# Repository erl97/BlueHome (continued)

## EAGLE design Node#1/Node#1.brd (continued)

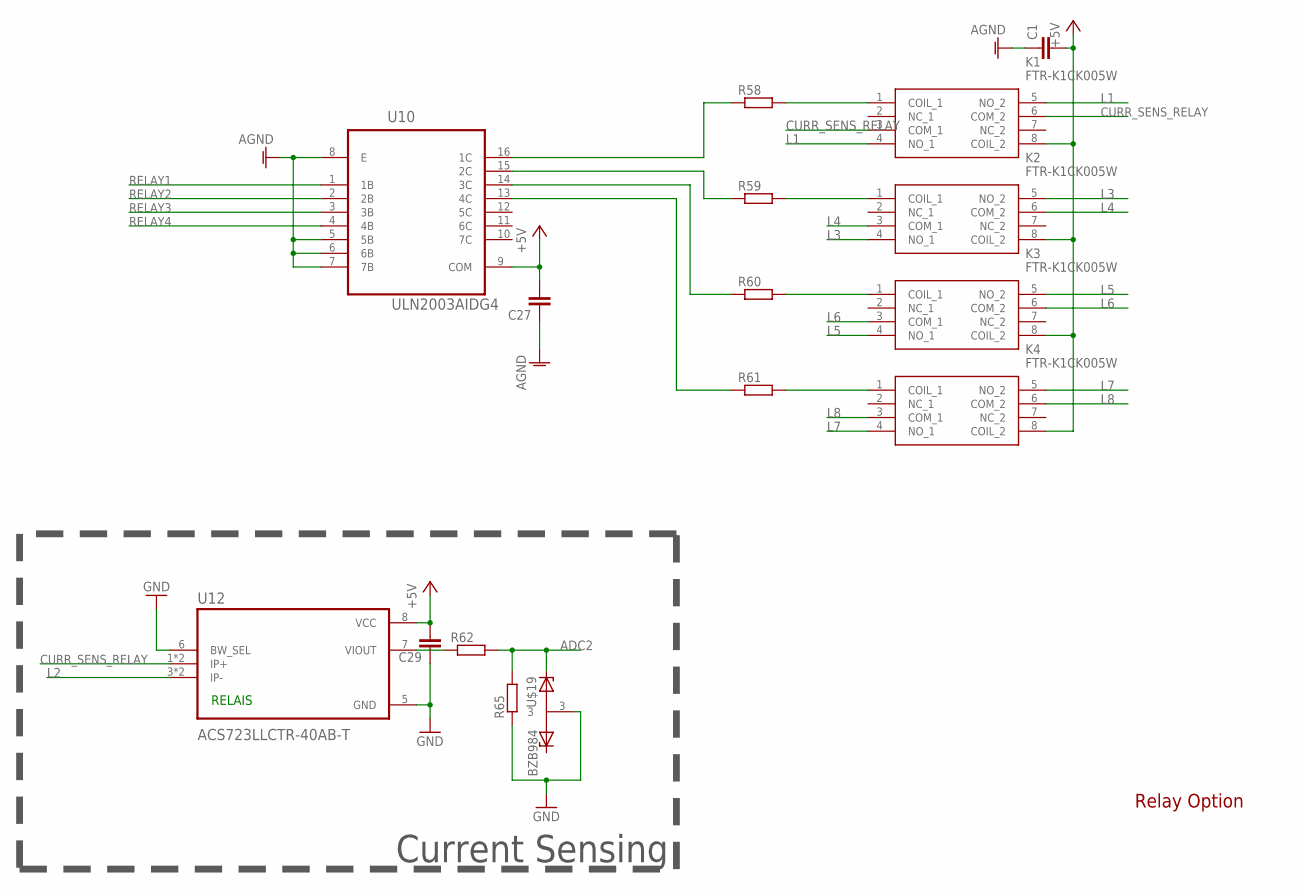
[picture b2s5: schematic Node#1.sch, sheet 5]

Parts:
C1, C27, C29: C-EUC0805; C0805
K1, K2, K3, K4: FTR-K1CK005W; FTRK1CK005W
R58, R59, R60, R61: R-EU_M0805; M0805
R62, R65: R-EU_R0805; R0805
U10: ULN2003AIDG4; SOIC127P600X175-16N
U12: ACS723LLCTR-40AB-T; SOIC127P600X175-8N
U$19: BZB984; SOT95P230X110-3N

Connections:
+5V: C1.2, C27.2, C29.2, K1.8 (COIL_2), K2.8 (COIL_2), K3.8 (COIL_2), K4.8 (COIL_2), U10.9 (COM), U12.8 (VCC); also elsewhere on the board
ADC2: R62.2, R65.2, U$19.1; also elsewhere on the board
AGND: C1.1, C27.1, U10.5 (5B), U10.6 (6B), U10.7 (7B), U10.8 (E); also elsewhere on the board
CURR_SENS_RELAY: K1.3 (COM_1), K1.6 (COM_2), U12.1 (IP+), U12.2 (IP+)
GND: C29.1, R65.1, U12.5 (GND), U12.6 (BW_SEL), U$19.3; also elsewhere on the board
L1: K1.4 (NO_1), K1.5 (NO_2); also elsewhere on the board
L2: U12.3 (IP-), U12.4 (IP-); also elsewhere on the board
L3: K2.4 (NO_1), K2.5 (NO_2); also elsewhere on the board
L4: K2.3 (COM_1), K2.6 (COM_2); also elsewhere on the board
L5: K3.4 (NO_1), K3.5 (NO_2); also elsewhere on the board
L6: K3.3 (COM_1), K3.6 (COM_2); also elsewhere on the board
L7: K4.4 (NO_1), K4.5 (NO_2); also elsewhere on the board
L8: K4.3 (COM_1), K4.6 (COM_2); also elsewhere on the board
unnamed: K1.1 (COIL_1), R58.2
unnamed: K2.1 (COIL_1), R59.2
unnamed: K3.1 (COIL_1), R60.2
unnamed: K4.1 (COIL_1), R61.2
unnamed: R58.1, U10.16 (1C)
unnamed: R59.1, U10.15 (2C)
unnamed: R60.1, U10.14 (3C)
unnamed: R61.1, U10.13 (4C)
unnamed: R62.1, U12.7 (VIOUT)
RELAY1: U10.1 (1B); also elsewhere on the board
RELAY2: U10.2 (2B); also elsewhere on the board
RELAY3: U10.3 (3B); also elsewhere on the board
RELAY4: U10.4 (4B); also elsewhere on the board

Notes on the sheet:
RELAIS
Current Sensing
Relay Option

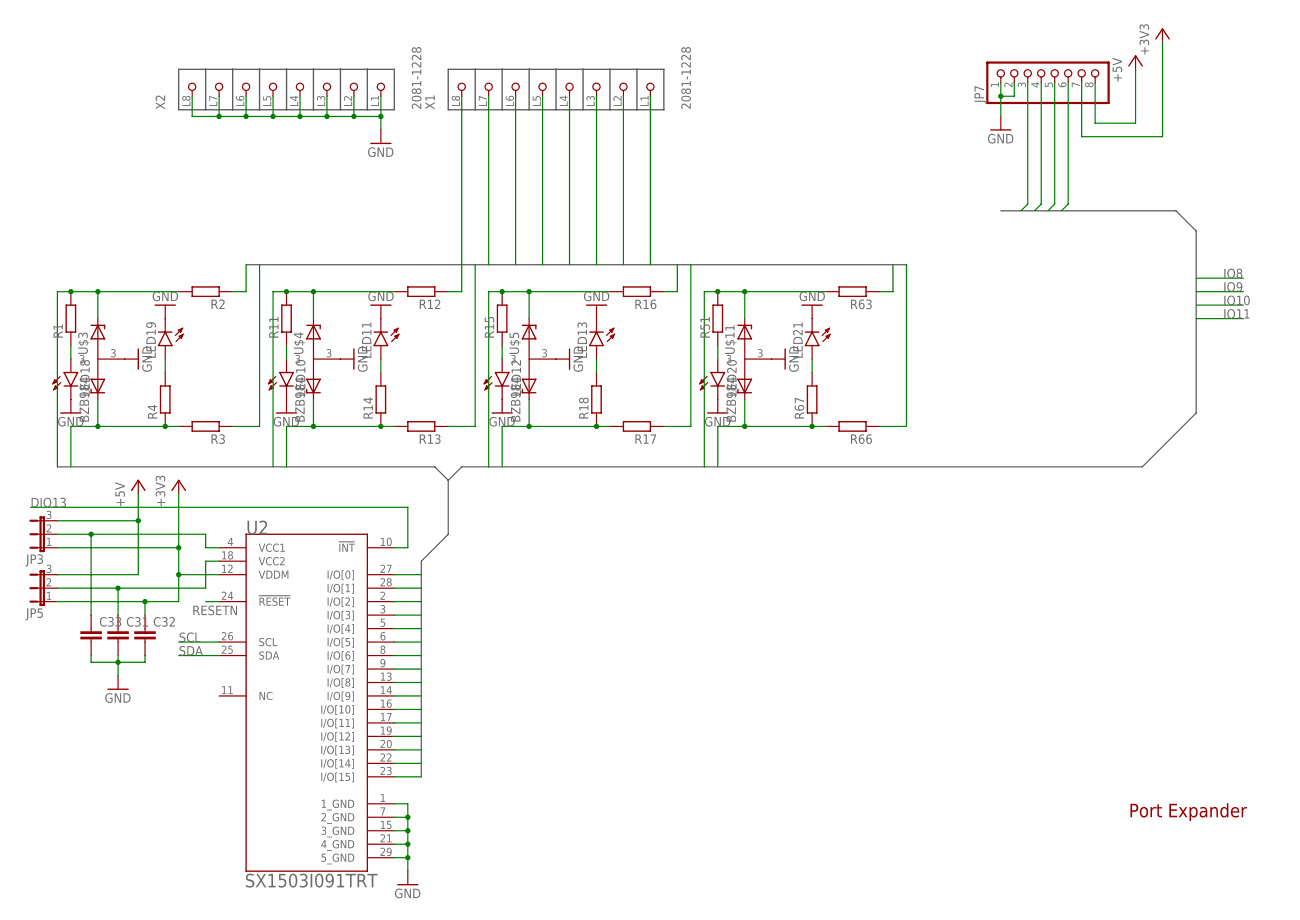
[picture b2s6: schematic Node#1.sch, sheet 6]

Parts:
C31, C32, C33: C-EUC0805; C0805
JP3, JP5: JP2E; JP2
JP7: PINHD-1X8; 1X08
LED10, LED11, LED12, LED13, LED18, LED19, LED20, LED21: LED3MM
R1, R2, R3, R4, R11, R12, R13, R14, R15, R16, R17, R18, R51, R63, R66, R67: R-EU_R0805; R0805
U2: SEMTECH_SX1503I091TRTSEMTECH_SX1503I091TRT_0_0; SEMTECH_SX1503I091TRT_0
U$3, U$4, U$5, U$11: BZB984; SOT95P230X110-3N
X1, X2: 2081-1228; P-2081-1228

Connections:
+3V3: C32.1, JP3.1, JP5.1, JP7.7, U2.12 (VDDM); also elsewhere on the board
+5V: JP3.3, JP5.3, JP7.8; also elsewhere on the board
DIO13: U2.10 (!INT!); also elsewhere on the board
GND: C31.2, C32.2, C33.2, JP7.1, JP7.2, LED10.K (C), LED11.K (C), LED12.K (C), LED13.K (C), LED18.K (C), LED19.K (C), LED20.K (C), LED21.K (C), U2.1 (1_GND), U2.7 (2_GND), U2.15 (3_GND), U2.21 (4_GND), U2.29 (5_GND), U$3.3, U$4.3, U$5.3, U$11.3, X2.L1 (P1), X2.L2 (P2), X2.L3 (P3), X2.L4 (P4), X2.L5 (P5), X2.L6 (P6), X2.L7 (P7), X2.L8 (P8); also elsewhere on the board
IO0: R1.2, R2.2, U2.27 (I/O[0]), U$3.1
IO1: R3.2, R4.1, U2.28 (I/O[1]), U$3.2
IO2: R11.2, R12.2, U2.2 (I/O[2]), U$4.1
IO3: R13.2, R14.1, U2.3 (I/O[3]), U$4.2
IO4: R15.2, R16.2, U2.5 (I/O[4]), U$5.1
IO5: R17.2, R18.1, U2.6 (I/O[5]), U$5.2
IO6: R51.2, R63.2, U2.8 (I/O[6]), U$11.1
IO7: R66.2, R67.1, U2.9 (I/O[7]), U$11.2
IO8: U2.13 (I/O[8]); also elsewhere on the board
IO9: U2.14 (I/O[9]); also elsewhere on the board
IO10: U2.16 (I/O[10]); also elsewhere on the board
IO11: U2.17 (I/O[11]); also elsewhere on the board
IO12: JP7.3, U2.19 (I/O[12])
IO13: JP7.4, U2.20 (I/O[13])
IO14: JP7.5, U2.22 (I/O[14])
IO15: JP7.6, U2.23 (I/O[15])
unnamed: LED18.A, R1.1
unnamed: LED19.A, R4.2
unnamed: LED10.A, R11.1
unnamed: LED11.A, R14.2
unnamed: LED12.A, R15.1
unnamed: LED13.A, R18.2
unnamed: LED20.A, R51.1
unnamed: LED21.A, R67.2
unnamed: C33.1, JP3.2, U2.4 (VCC1)
unnamed: C31.1, JP5.2, U2.18 (VCC2)
O_IO0: R2.1, X1.L1 (P1)
O_IO1: R3.1, X1.L2 (P2)
O_IO2: R12.1, X1.L3 (P3)
O_IO3: R13.1, X1.L4 (P4)
O_IO4: R16.1, X1.L5 (P5)
O_IO5: R17.1, X1.L6 (P6)
O_IO6: R63.1, X1.L7 (P7)
O_IO7: R66.1, X1.L8 (P8)
RESETN: U2.24 (!RESET!); also elsewhere on the board
SCL: U2.26 (SCL); also elsewhere on the board
SDA: U2.25 (SDA); also elsewhere on the board

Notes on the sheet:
Port Expander

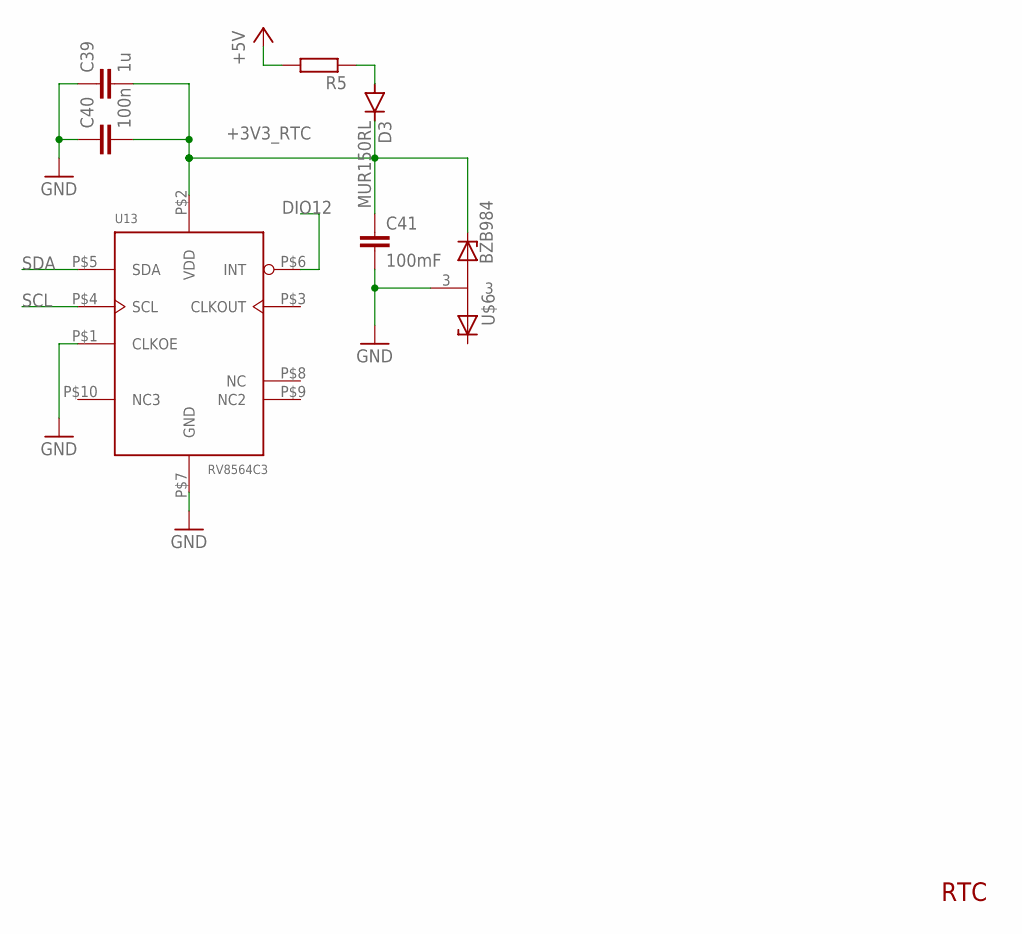
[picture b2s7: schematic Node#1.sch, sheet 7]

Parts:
C39: 1u; C0805
C40: 100n; C0805
C41: 100mF; C050-055X075
D3: MUR150RL; DO41-10
R5: R-EU_R0805; R0805
U13: RV8564C3; RTC-C3
U$6: BZB984; SOT95P230X110-3N

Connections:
+3V3_RTC: C39.2, C40.2, C41.1, D3.C, U13.P$2 (VDD), U$6.2
+5V: R5.2; also elsewhere on the board
DIO12: U13.P$6 (INT); also elsewhere on the board
GND: C39.1, C40.1, C41.2, U13.P$1 (CLKOE), U13.P$7 (GND), U$6.3; also elsewhere on the board
unnamed: D3.A, R5.1
SCL: U13.P$4 (SCL); also elsewhere on the board
SDA: U13.P$5 (SDA); also elsewhere on the board

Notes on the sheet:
RTC

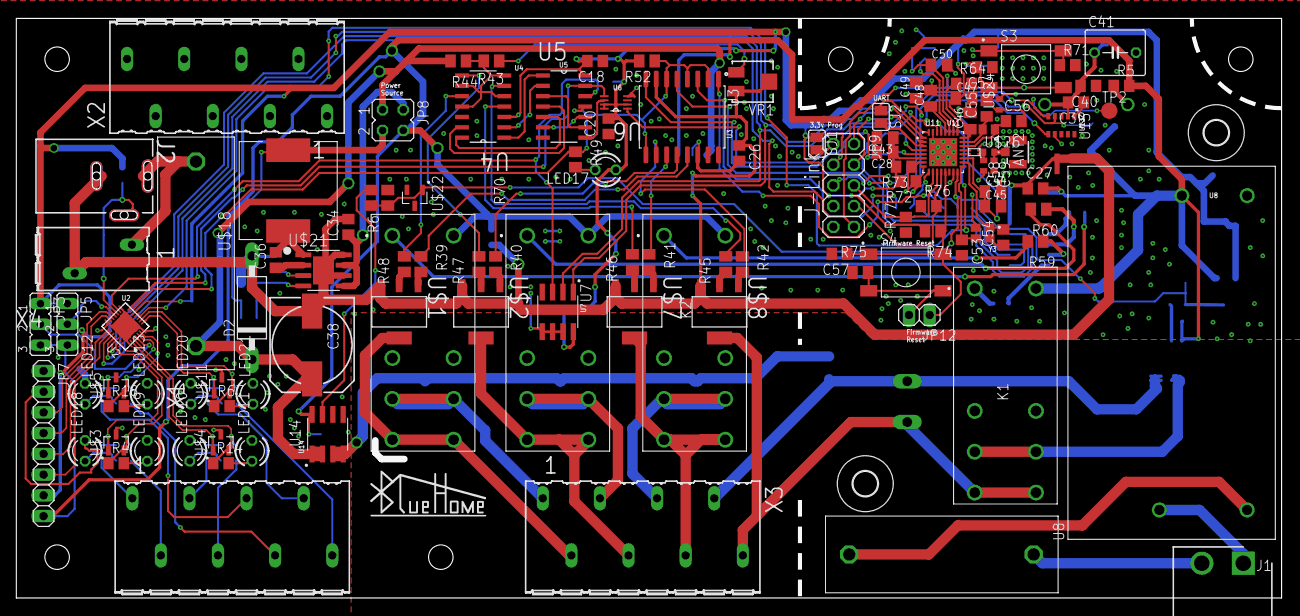
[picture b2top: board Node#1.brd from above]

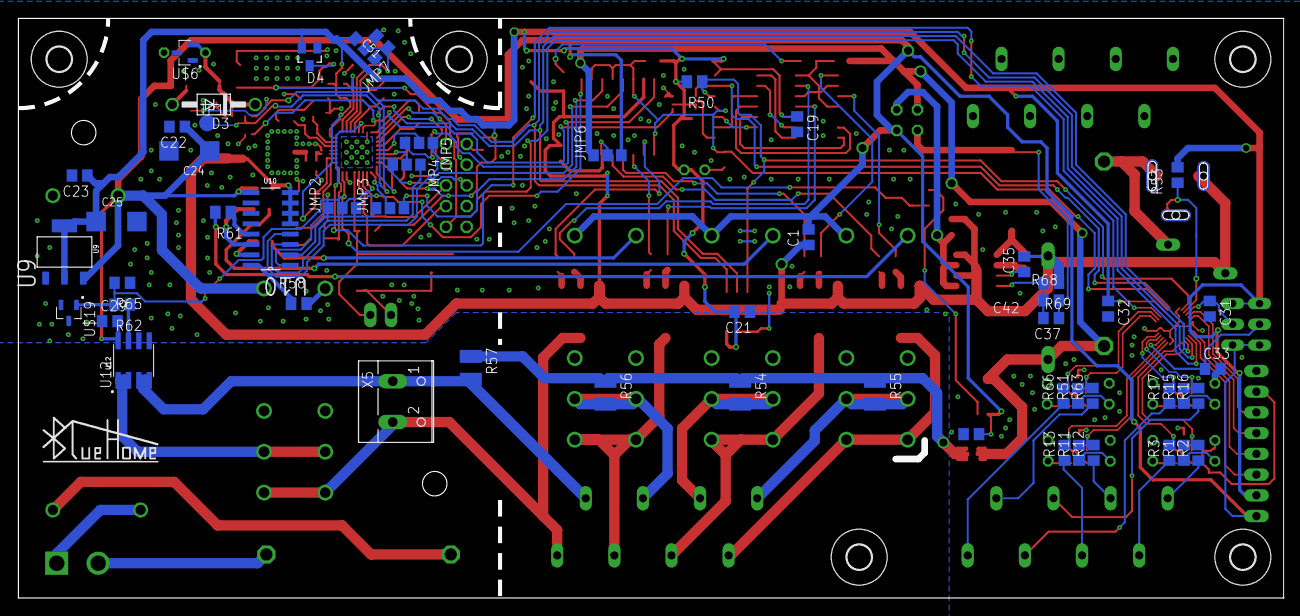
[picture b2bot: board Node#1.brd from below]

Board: 2 copper layers, 155.0 x 71.0 mm, 179 parts (59 on the bottom side), 134 nets.

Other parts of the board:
U$10, U$12, U$13, U$14, U$15, U$16, U$17: 3,0

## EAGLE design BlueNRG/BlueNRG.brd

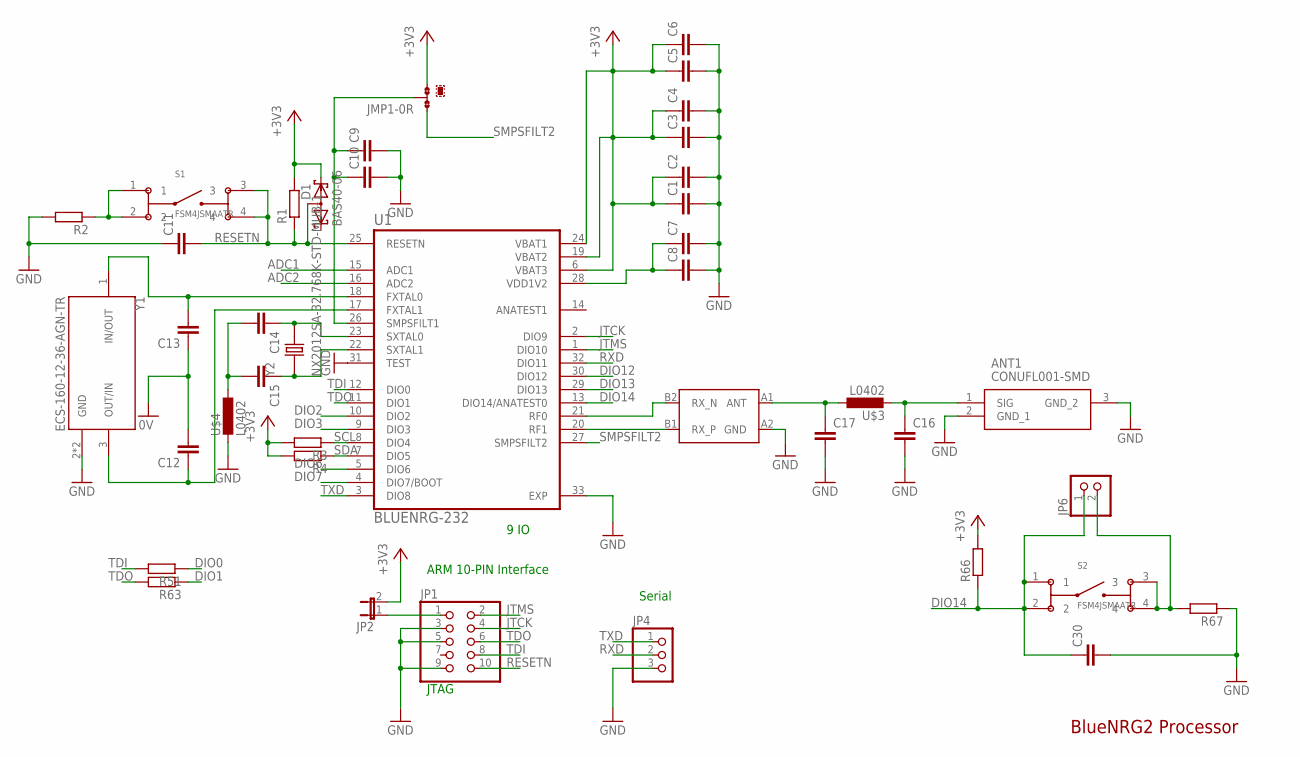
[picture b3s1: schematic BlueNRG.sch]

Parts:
ANT1: CONUFL001-SMD
C1, C2, C3, C4, C5, C6, C7, C8, C9, C10: C-EUC0805K; C0805K
C11, C12, C13, C14, C15, C30: C-EUC0805; C0805
C16, C17: C-EUC0402; C0402
D1: BAS40-06; SOT23
JMP1: 0R-JUMPA; A0R-JMP
JP1: PINHD-2X5; 2X05
JP2: JP1E; JP1
JP4: PINHD-1X3; 1X03
JP6: PINHD-1X2; 1X02
R1, R2, R3, R4, R51, R63: R-EU_R0805; R0805
R66, R67: R-EU_R1210; R1210
S1, S2: FSM4JSMAATR; SW_FSM4JSMAATR
U1: BLUENRG-232; QFN50P500X500X100-33T345N
U$3, U$4: L0402; R0402
U$5: BALF-NRG-01D3; FLIPCHIP
Y1: ECS-160-12-36-AGN-TR; XTAL_ECS-160-12-36-AGN-TR
Y2: NX2012SA-32.768K-STD-MUB-1; XTAL_NX2012SA-32.768K-STD-MUB-1

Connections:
0V: C12.2, C13.1
+3V3: C1.1, C2.1, C3.1, C4.1, C5.1, C6.1, D1.2 (K2), JMP1.3, JP2.2, R1.2, R3.2, R4.2, R66.2, U1.6 (VBAT3), U1.19 (VBAT2), U1.24 (VBAT1)
ADC1: U1.15 (ADC1)
ADC2: U1.16 (ADC2)
DIO0: R51.1
DIO1: R63.1
DIO2: U1.10 (DIO2)
DIO3: U1.9 (DIO3)
DIO6: U1.5 (DIO6)
DIO7: U1.4 (DIO7/BOOT)
DIO12: U1.30 (DIO12)
DIO13: U1.29 (DIO13)
DIO14: C30.1, JP6.1, R66.1, S2.1, S2.2, U1.13 (DIO14/ANATEST0)
GND: ANT1.2 (GND_1), ANT1.3 (GND_2), C1.2, C2.2, C3.2, C4.2, C5.2, C6.2, C7.2, C8.2, C9.2, C10.2, C11.1, C16.2, C17.2, C30.2, JP1.3, JP1.5, JP1.9, JP4.3, R2.2, R67.1, U1.31 (TEST), U1.33 (EXP), U$4.2, U$5.A2 (GND), Y1.2 (GND), Y1.4 (GND)
JTCK: JP1.4, U1.2 (DIO9)
JTMS: JP1.2, U1.1 (DIO10)
unnamed: C7.1, C8.1, U1.28 (VDD1V2)
unnamed: C9.1, C10.1, JMP1.2, U1.26 (SMPSFILT1)
unnamed: JP1.1, JP2.1
unnamed: C12.1, U1.17 (FXTAL1), Y1.3 (OUT/IN)
unnamed: R2.1, S1.1, S1.2
unnamed: C13.2, U1.18 (FXTAL0), Y1.1 (IN/OUT)
unnamed: U1.21 (RF0), U$5.B2 (RX_N)
unnamed: U1.20 (RF1), U$5.B1 (RX_P)
unnamed: C14.2, C15.2, U$4.1
unnamed: C14.1, U1.23 (SXTAL0), Y2.2
unnamed: C15.1, U1.22 (SXTAL1), Y2.1
unnamed: C17.1, U$3.1, U$5.A1 (ANT)
unnamed: ANT1.1 (SIG), C16.1, U$3.2
unnamed: JP6.2, R67.2, S2.3, S2.4
RESETN: C11.2, D1.3 (AA), JP1.10, R1.1, S1.3, S1.4, U1.25 (RESETN)
RXD: JP4.2, U1.32 (DIO11)
SCL: R3.1, U1.8 (DIO4)
SDA: R4.1, U1.7 (DIO5)
SMPSFILT2: JMP1.1, U1.27 (SMPSFILT2)
TDI: JP1.8, R51.2, U1.12 (DIO0)
TDO: JP1.6, R63.2, U1.11 (DIO1)
TXD: JP4.1, U1.3 (DIO8)

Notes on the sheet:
JTAG
ARM 10-PIN Interface
9 IO
Serial
BlueNRG2 Processor

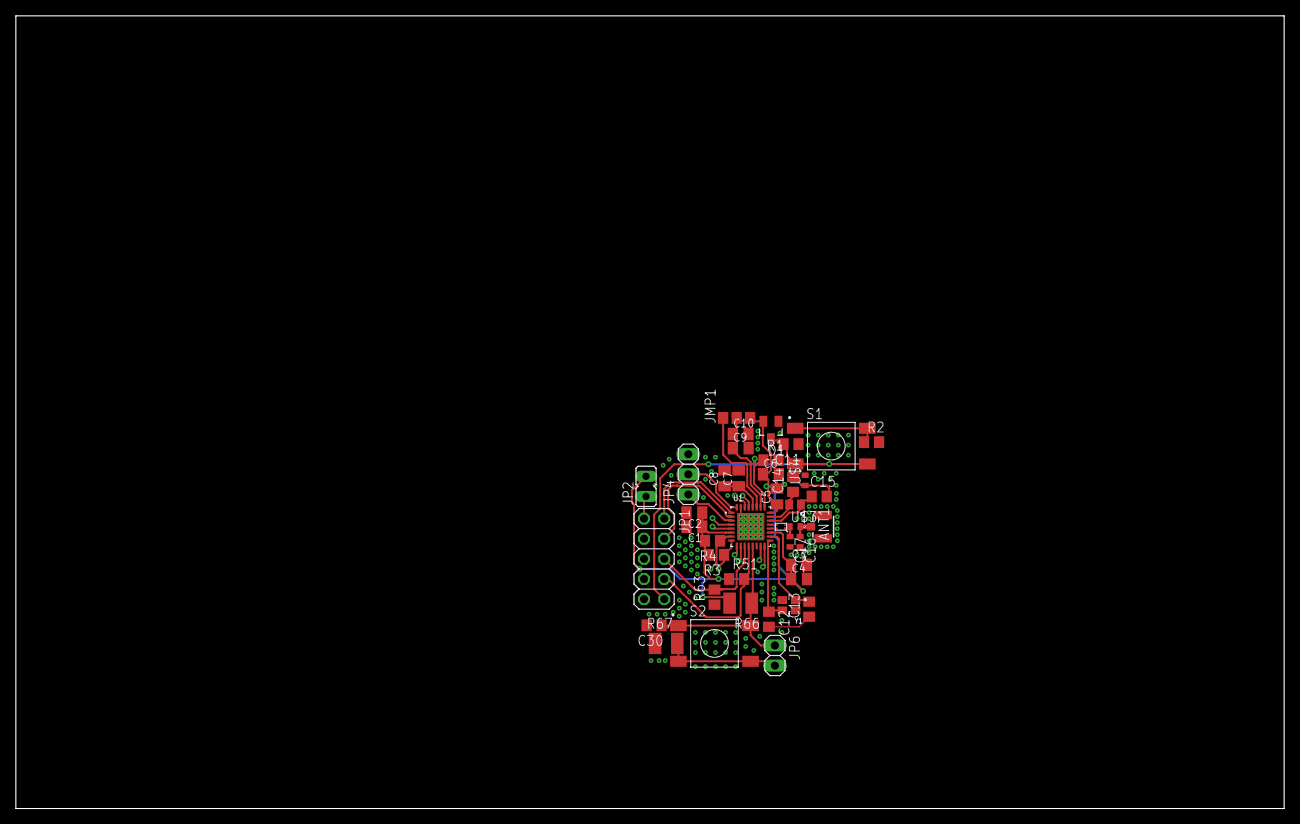
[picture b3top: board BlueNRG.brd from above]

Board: 2 copper layers, 160.0 x 100.0 mm, 41 parts (0 on the bottom side), 28 nets.

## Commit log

2018-11-19 Initial Schematics
2018-11-19 Changed directories
2018-11-19 Deleted old files
2018-11-20 Demo Commit - Updated Readme
2018-12-03 Added Custom Library
2018-12-10 Added Parts to lib
2018-12-10 Initial Layout
2018-12-17 Modified Lib, Node#1
2018-12-17 Modified library, Node #1 BlueNRG
2018-12-17 Node#2 modified
2018-12-17 Modified Node#1
2019-01-09 Finished BlueNRG
2019-01-10 Node #2 Update
2019-01-10 Missing files
2019-01-10 Node 2 Power, i2 modiefied
2019-01-10 Node 2 Power, i2 modiefied + missing Files
2019-01-10 Finished BlueNRG 2; Added IO-Expander
2019-01-14 Output Driver Node#1
2019-01-15 node2 modified
2019-01-15 Update LBR
2019-01-15 Updated Lib - Touch Controller
2019-01-15 Update Endstufe Absicherung
2019-01-15 node 2 display
2019-01-18 Updated Library
2019-01-18 Updated Library Touch Buttons
2019-01-18 Node#1 update
2019-01-21 restored
2019-01-21 Node#1
2019-01-21 bi-colour_leds
2019-01-21 small changes
2019-01-23 node2 spi, rtc
2019-01-23 Node#2 sorted, Node#1 small adjusts
2019-01-24 Schematic finished (hopefully) !
2019-01-28 Changed Packages, connected GPIO
2019-02-04 Created node#2 Layout and Proximity Sensor in Library
2019-02-04 Created BlueNRG Design Block and Board Size for Node#1
2019-02-05 Added lager Board Layout in Node#1
2019-02-05 Worked on Layout on Node#2
2019-02-05 Layout von Node#2 fertiggestellt
2019-02-05 Worked on Layout for Node#1
2019-02-07 Initial V2
2019-02-07 Init
2019-02-07 Placed Buttons and Display
2019-02-07 Display gedreht, Diodenfootprints
2019-02-08 Redone Node#1 Layout
2019-02-08 buttons
2019-02-08 Arrangement of Node#1 - DC Power Jack
2019-02-11 Layout: touchbuttons, power
2019-02-11 worked on Layout
2019-02-12 added 6-parted wheel to library
2019-02-12 (hopefully) Finished Layout
2019-02-13 Resolve Merge Error in Lib
2019-02-13 finished Layout (again), added Testpoints
2019-02-13 Lib changed after merge problem
2019-02-13 saved nothing
2019-02-13 display
2019-02-14 Finished Layout Node#2
2019-02-18 finished again
2019-02-19 beautyfied
2019-02-19 Last changes for ordering
2019-02-19 print version
